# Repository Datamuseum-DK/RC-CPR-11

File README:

This repository contains the KiCad schematic files for
the RegneCentralen CPR-11 modulus-11 checker.

For more information: https://datamuseum.dk/wiki/RC/CPR-11

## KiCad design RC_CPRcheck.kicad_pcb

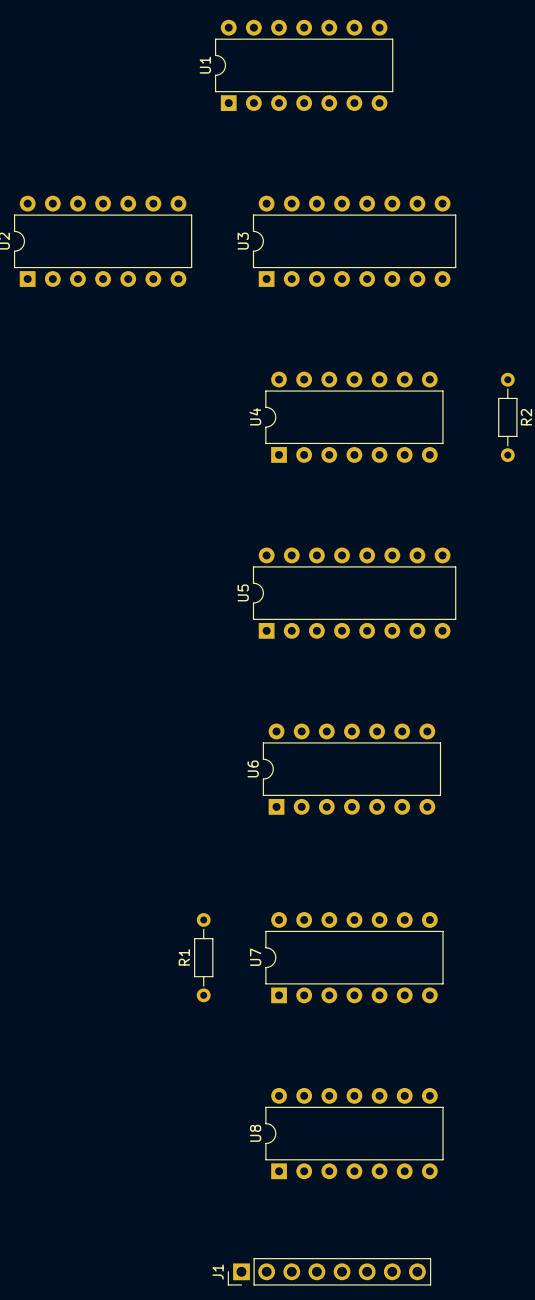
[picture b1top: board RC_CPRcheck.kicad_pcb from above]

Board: 2 copper layers, 11 parts (0 on the bottom side), 29 nets, no tracks yet.

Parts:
J1: Conn_01x08_Male; PinHeader_1x08_P2.54mm_Vertical
R1, R2: 15k; R_Axial_DIN0204_L3.6mm_D1.6mm_P7.62mm_Horizontal
U1: 74LS90; DIP-14_W7.62mm
U2: 74LS40; DIP-14_W7.62mm
U3: 74LS76; DIP-16_W7.62mm
U4: 74LS00; DIP-14_W7.62mm
U5: 74167; DIP-16_W7.62mm
U6: 7451; DIP-14_W7.62mm
U7, U8: 74LS74; DIP-14_W7.62mm

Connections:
GND: J1.2, U1.6 (R9(1)), U1.7 (R9(2)), U1.10 (GND), U2.7 (GND), U3.5 (VCC), U3.12 (K), U4.7 (GND), U5.3 (B3), U5.4 (SET-TO-9), U5.8 (GND), U5.10 (STROBE), U5.11 (ENABLE), U5.12 (UNITY/CAS), U6.7 (GND), U7.7 (GND), U8.7 (GND)
unnamed: J1.3, U5.9 (CLK)
unnamed: J1.4, U2.4, U3.2 (~S), U3.8 (~R), U4.1, U4.2, U7.1 (~R), U7.10 (~S), U8.1 (~R), U8.10 (~S)
unnamed: J1.5, U8.3 (C)
unnamed: J1.6, U2.6
unnamed: J1.7, U2.8
unnamed: R2.2, U3.7 (~S)
unnamed: U1.1 (CP1..3), U1.12 (Q0)
unnamed: U1.2 (R0(1)), U1.3 (R0(2)), U2.1, U3.9 (J), U3.15 (Q)
unnamed: U1.11 (Q3), U3.1 (C)
unnamed: U1.14 (CP0), U3.6 (C), U5.5 (Z)
unnamed: U2.9, U3.14 (~Q)
unnamed: U2.10, U6.5, U6.9, U8.8 (~Q), U8.12 (D)
unnamed: U2.2, U2.12, U4.8
unnamed: U2.5, U2.13, U8.2 (D), U8.6 (~Q)
unnamed: U3.3 (~R), U3.4 (J)
unnamed: U3.10 (~Q), U3.16 (K)
unnamed: U4.9, U4.10, U4.11
unnamed: U4.12, U6.1, U6.4, U7.8 (~Q), U7.12 (D)
unnamed: U4.13, U6.13, U7.2 (D), U7.6 (~Q)
unnamed: U5.2 (B2), U6.8
unnamed: U4.3, U5.13 (CLR)
unnamed: U5.14 (B0), U8.5 (Q), U8.11 (C)
unnamed: U5.15 (B1), U6.6
unnamed: U6.2, U7.3 (C), U8.9 (Q)
unnamed: U6.3, U6.10, U7.9 (Q)
unnamed: U7.5 (Q), U7.11 (C)
unnamed: R1.2, U7.4 (~S), U7.13 (~R), U8.4 (~S), U8.13 (~R)
VCC: J1.1, R1.1, R2.1, U1.5 (VCC), U2.14 (VCC), U3.13 (GND), U4.14 (VCC), U5.16 (VCC), U6.14 (VCC), U7.14 (VCC), U8.14 (VCC)

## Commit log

2023-05-08 First checkin
2023-05-08 Add Readme
2023-05-08 Fix link
